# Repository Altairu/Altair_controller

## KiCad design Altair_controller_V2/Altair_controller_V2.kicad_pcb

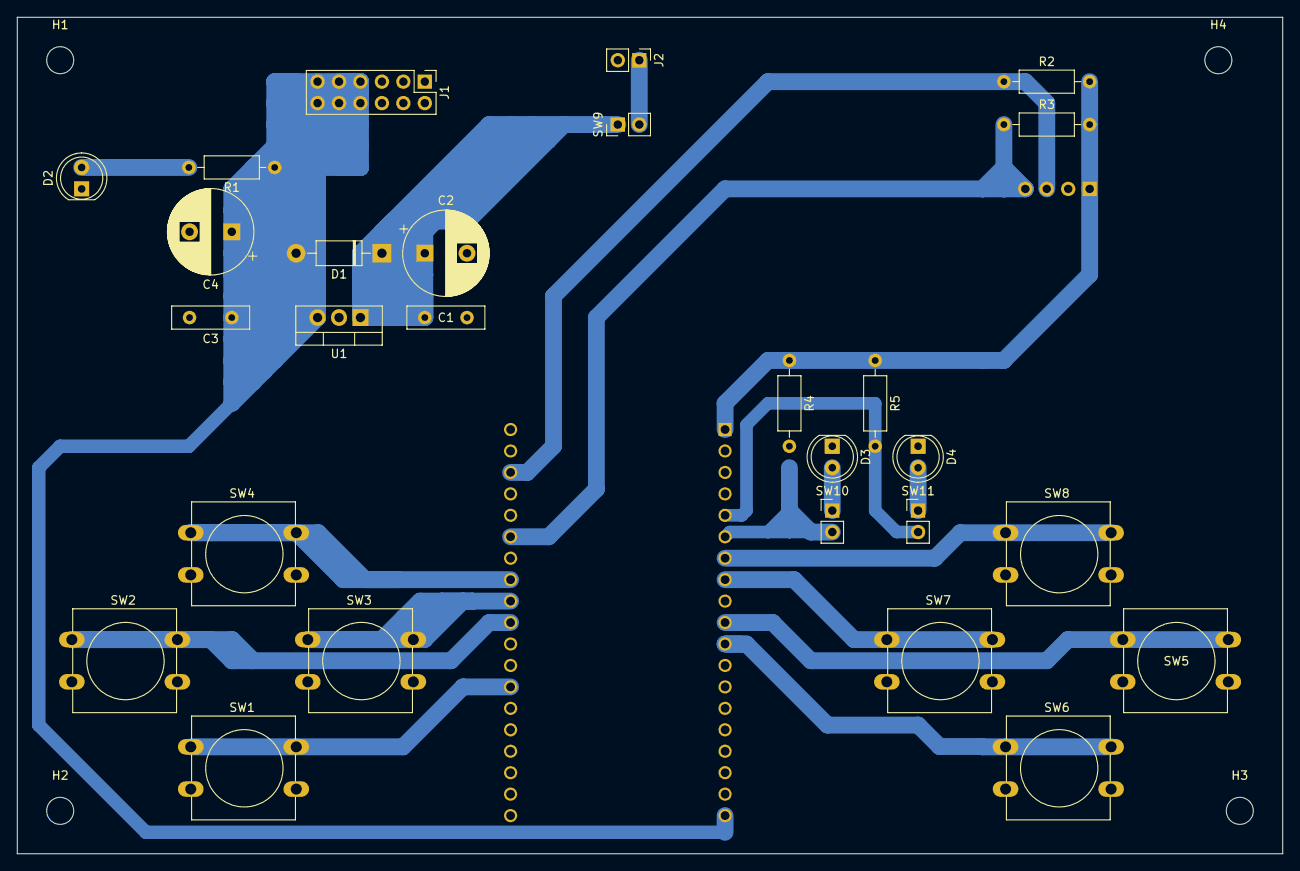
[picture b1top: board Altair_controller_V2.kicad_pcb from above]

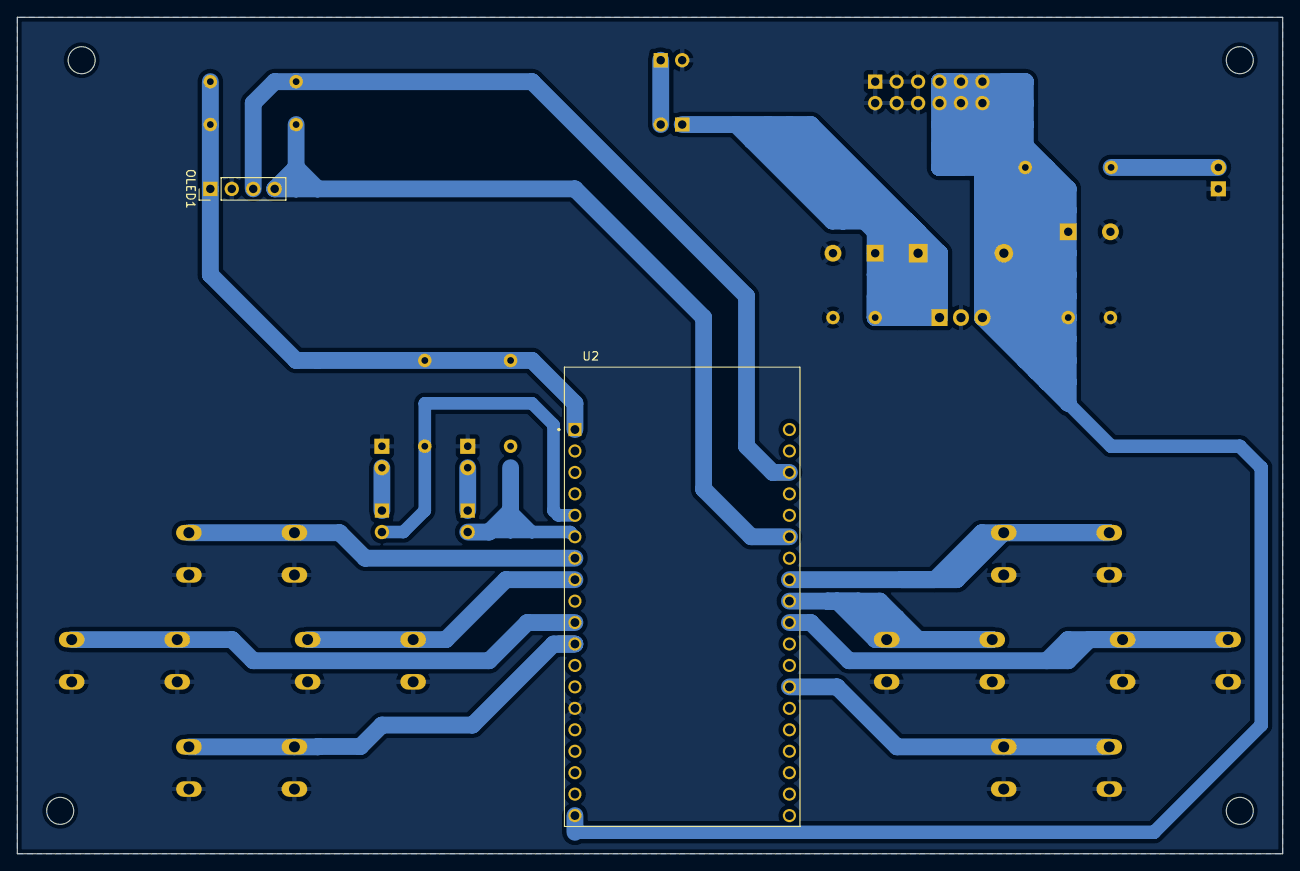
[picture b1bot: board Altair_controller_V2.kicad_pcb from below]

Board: 2 copper layers, 149.9 x 99.1 mm, 33 parts (2 on the bottom side), 20 nets.

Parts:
C1, C3: 0.1μF; C_Disc_D9.0mm_W2.5mm_P5.00mm
C2, C4: 10uF～100uF; CP_Radial_D10.0mm_P5.00mm
D1: D_Schottky; D_DO-41_SOD81_P10.16mm_Horizontal
D2, D3, D4: LED; LED_D5.0mm
H1, H2, H3, H4: MountingHole; MountingHole_3.2mm_M3
J1: Conn_02x06_Odd_Even; PinHeader_2x06_P2.54mm_Vertical
J2: Conn_01x02_Female; PinHeader_1x02_P2.54mm_Vertical
OLED1: OLED; PinHeader_1x04_P2.54mm_Vertical
R1: 510; R_Axial_DIN0207_L6.3mm_D2.5mm_P10.16mm_Horizontal
R2, R3: 10k; R_Axial_DIN0207_L6.3mm_D2.5mm_P10.16mm_Horizontal
R4, R5: 220; R_Axial_DIN0207_L6.3mm_D2.5mm_P10.16mm_Horizontal
SW1, SW2, SW3, SW4, SW5, SW6, SW7, SW8: SW_Push_Dual; SW_PUSH-12mm
SW9, SW10, SW11: SW_DIP_x01; PinHeader_1x02_P2.54mm_Vertical
U1: 7805; TO-220-3_Vertical
U2: ESP32-DEVKITC-32D; MODULE_ESP32-DEVKITC-32D

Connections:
1: SW5.1, U2.J2-10 (IO26)
2: SW6.1, U2.J2-11 (IO27)
3: SW7.1, U2.J2-8 (IO33)
4: SW8.1, U2.J2-7 (IO32)
5: R4.2, SW10.2, U2.J2-6 (IO35)
6: R5.2, SW11.2, U2.J2-5 (IO34)
+3.3V: OLED1.1, R2.2, R3.2, R4.1, R5.1, U2.J2-1 (3V3)
+5V: C3.1, C4.1, D1.2 (A), J1.7, J1.8, J1.9, J1.10, J1.11, J1.12, R1.1, U1.3 (VO), U2.J2-19 (EXT_5V)
A: SW1.1, U2.J3-13 (IO4)
B: SW2.1, U2.J3-10 (IO5)
C: SW3.1, U2.J3-9 (IO18)
D: SW4.1, U2.J3-8 (IO19)
GND: C1.2, C2.2, C3.2, C4.2, D2.1 (K), D3.1 (K), D4.1 (K), J1.1, J1.2, J1.3, J1.4, J1.5, J1.6, J2.2, OLED1.2, SW1.2, SW2.2, SW3.2, SW4.2, SW5.2, SW6.2, SW7.2, SW8.2, U1.2 (GND), U2.J2-14 (GND1)
unnamed: C1.1, C2.1, D1.1 (K), SW9.1, U1.1 (VI)
unnamed: D2.2 (A), R1.2
unnamed: D3.2 (A), SW10.1
unnamed: D4.2 (A), SW11.1
SCL: OLED1.3, R2.1, U2.J3-3 (IO22)
SDA: OLED1.4, R3.1, U2.J3-6 (IO21)
VCC: J2.1, SW9.2
